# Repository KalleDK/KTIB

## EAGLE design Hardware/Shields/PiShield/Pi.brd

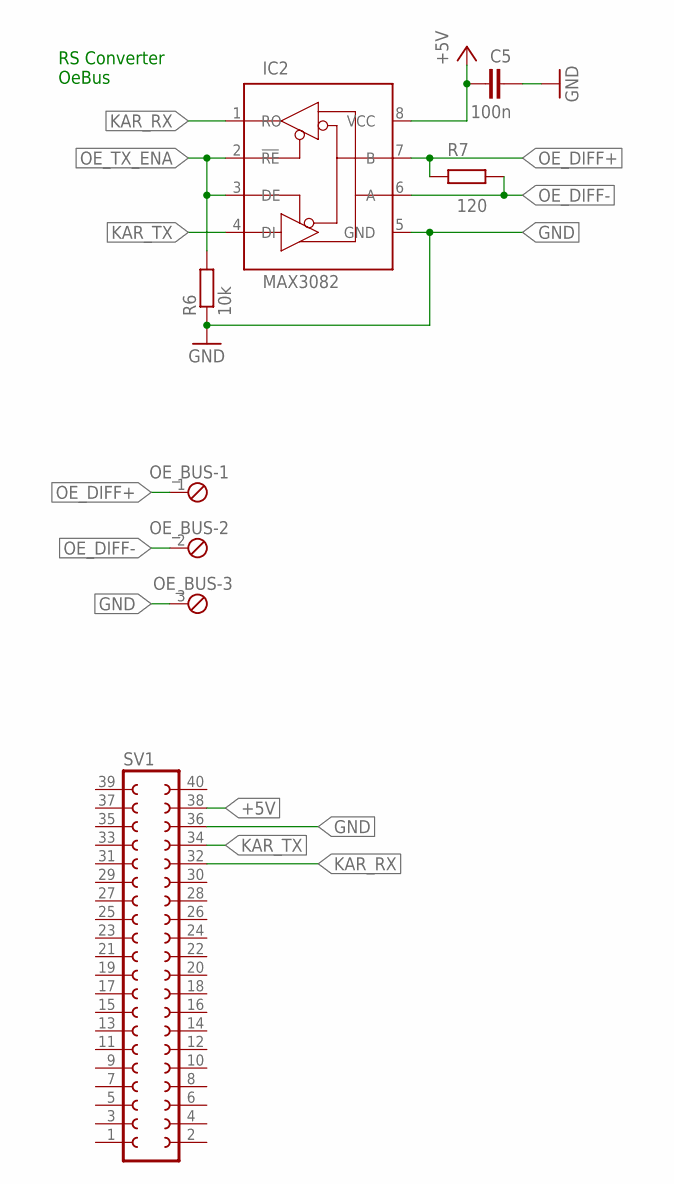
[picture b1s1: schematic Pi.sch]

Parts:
C5: 100n; C5B3
IC2: MAX3082; DIL08
OE_BUS: MPT3; 3POL254
R6: 10k; 0207/12
R7: 120; 0207/12
SV1: FE20-2

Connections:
+5V: SV1.38
GND: C5.2, IC2.5 (GND), OE_BUS.3, R6.1, SV1.36
KAR_RX: IC2.1 (RO), SV1.32
KAR_TX: IC2.4 (DI), SV1.34
OE_DIFF+: IC2.7 (B), OE_BUS.1, R7.2
OE_DIFF-: IC2.6 (A), OE_BUS.2, R7.1
OE_TX_ENA: IC2.2 (!RE!), IC2.3 (DE), R6.2
VCC: C5.1, IC2.8 (VCC)

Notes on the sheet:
RS Converter OeBus

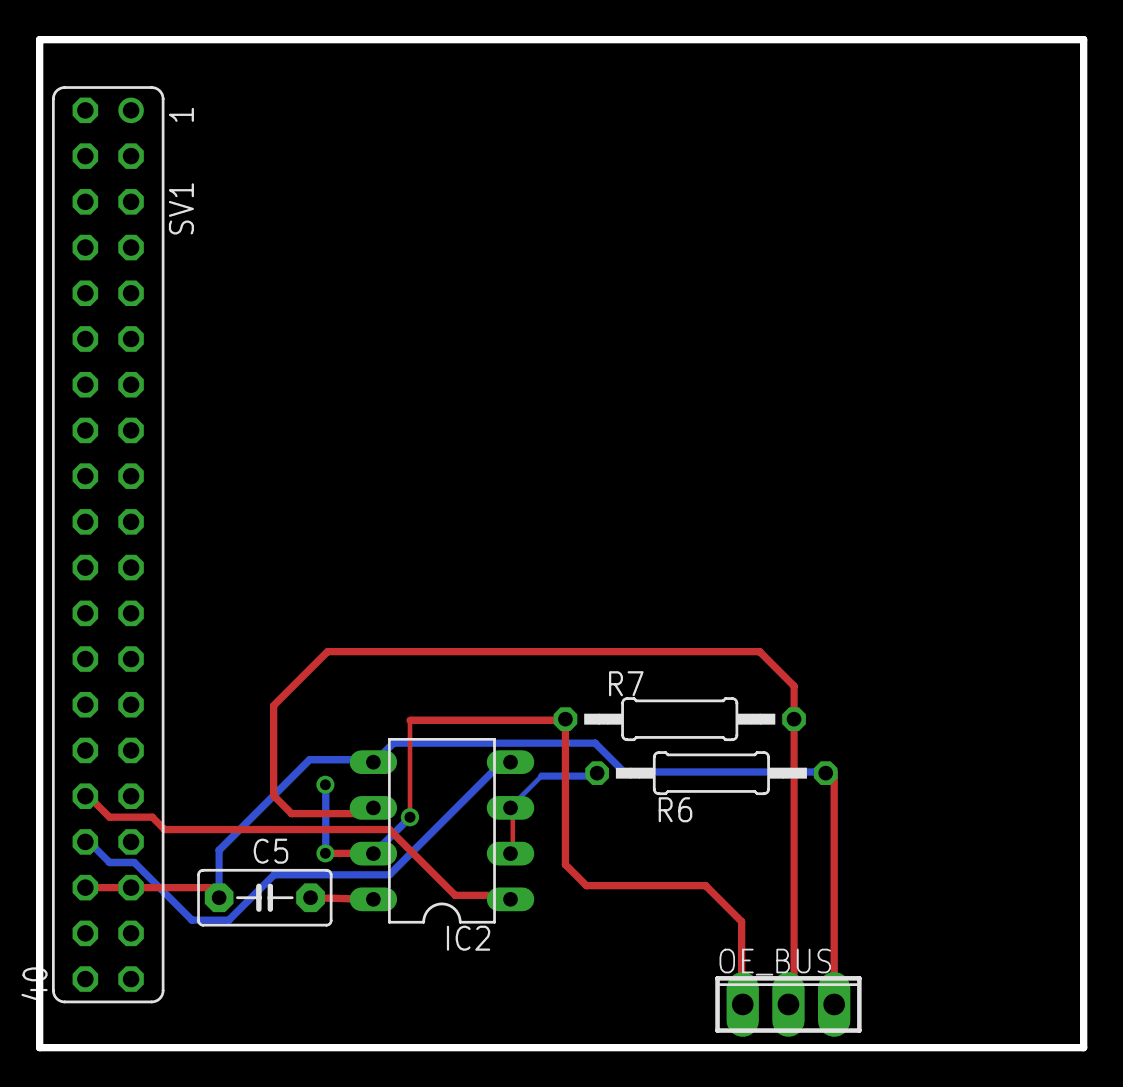
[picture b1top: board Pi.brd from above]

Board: 2 copper layers, 58.0 x 56.0 mm, 6 parts (0 on the bottom side), 7 nets.

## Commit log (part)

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2015-03-16 Systemarkitektur
2015-03-16 Fixes #40
2015-03-16 Ændringer til use case 2,3,4 og oprettelse af 5 og 6
    Oprettede use case 7 kalibrer pH-probe
    Ændringer fra i formiddags
    Flere rettelser
2015-03-17 Flyttet diagrammer
    Diagrammer er flyttet fra dropbox og ind i git, der er også oprettet
    mapper til system arkitektur
2015-03-17 Tilføjet Datablade
    Datablade til RS232 til RS485 konverteren
2015-03-17 opdaterede diagrammer KE
2015-03-17 KarControl added KE
2015-03-17 oprydning KE
2015-03-17 edits diagrammer KE
2015-03-17 Systemdiagram opdateret KE
2015-03-17 AVS domain model opdateret KE
2015-03-17 PSoC er weird
2015-03-17 flowchart added
2015-03-17 Rettelser til diagrammer
    Tilføjet og rettet i diverse diagrammer
2015-03-18 Opsætning af dokument til sys ark
    Har sat dokumentet op til system ark
2015-03-18 KarControl edits KE
2015-03-18 edit AVS domain model KE
2015-03-18 edits KarControldiagrammer KE
2015-03-18 Convert To PNG
2015-03-18 Ændret navne på visio filer og sat tex op
2015-03-18 Rettet visiofiler til kun at have en side
2015-03-18 Opdaterede system ark tex
2015-03-18 Der er lavet indtil videre
2015-03-18 Sensor Ø Allokerings diagram
    Sensor Ø BDD diagram
    Sensor Ø BDD opdateret
    BDD Opdateret og IBD
    IBD Implementeret
    Rettelse af IBD og BDD
2015-03-18 Ventilstyring rettet til
2015-03-18 Rettet navne og inout
2015-03-18 Sensor Library Added
2015-03-18 Ændres BDD og IBD pH-probe og jordfugt
2015-03-18 phProbe opdateret
2015-03-18 Jordfugt bdd og ibd opdateret
2015-03-18 IBD + BDD rettelser
2015-03-18 Domain model rettet
2015-03-18 nye png'er
2015-03-18 edits KE
2015-03-18 Signal beskrivelser
    For karcontrol
2015-03-18 Indsat beskriveleser
2015-03-18 Rettelser og beskrivelser
    I sys ark
2015-03-18 Vandpumpe indsat i tex
2015-03-18 Update af PNG
2015-03-18 Update af PNG'er
2015-03-18 Signal beskrivelser
2015-03-18 Små rettelser
2015-03-19 Massive oprydning og flere funktioner
2015-03-19 AllokeringsDiagram -> Allokeringsdiagram
2015-03-19 Noget vi ikke snakker om :panda_face:
2015-03-20 Indsat massere af fixmes
2015-03-20 fixes#116
2015-03-20 CentralControl_signalbeskrivelse_rettet #118
2015-03-20 KarControl edit KE #118
2015-03-20 Sesnor Ø + KarControl edits KE #118
2015-03-20 Fieldsensor edits KE #118
2015-03-20 Sensor_Jordfugt edits KE #118
2015-03-23 Opdateret UC og aktør diagrammer
2015-03-23 Fjernet plante som aktør og rette UC1
    Har rettet UC1 så denne ligner de andre UC
2015-03-23 Fjernet fixmes
2015-03-23 fixme update KE
2015-03-23 fixe update KE
2015-03-23 Sensor_pH diagrammer update KE
2015-03-23 signalbeskrivelse update KE
2015-03-23 Diagrammer edits KE
2015-03-24 gitignore upadte KE
2015-03-24 Pumpe+ventil forsyning edit KE
2015-03-24 Moved balde to blade
2015-03-25 Systems overordnede SD
2015-03-25 Sensor Ø Statemachine og Polling af Fieldsensors
2015-03-25 Tilføjet note
2015-03-26 Opdateret diagram
2015-03-27 PSU tilføjet til KarControl BDD/IBD
    PSU og RSConverter systemarkitektur aflyst
2015-03-31 Doseringspumpe + tex added KE
2015-04-03 Gitignore og header lavet for psoc
2015-04-03 Fieldsensor skabelon
2015-04-03 RS485 Protocol test
2015-04-03 Topdesign
2015-04-03 Rettet headerfil
2015-04-03 SensorOE I2C Done
2015-04-03 Intro Uart
2015-04-04 Removed all unused
2015-04-04 Updated SensorOe
    Changed from MsgQue to Bus
    And sender to transmitter
2015-04-04 Rettet hardcoded adresser
2015-04-04 tex updated med alaign KE
2015-04-04 HW- Ventilstyring added KE
    Ventilstyring i tex added KE
    tex updateret med align KE
2015-04-04 Beskrivelse af design til jordfugt og pH
    Design af jord fugtmåleren er beskrevet
2015-04-08 Interface beskrivelse i kravS.
    ordet planter fjernet fra Use case beskrivelsen.
2015-04-09 AVS Psoc Library
    SensorBus start
    RS485 uint16 to uint8
    Many changes to the lib
    Moved clear due to timing issue
    Fieldsensor complete
    Update topdesign
2015-04-09 Jordfugt tilføjet
    Software til PH probe tilføjet
    Debug added
    Move PHProbe
2015-04-09 Jordfugt opdateret
2015-04-10 Flow_Sensor_teknologiundersøgelse tex. added KE
2015-04-12 Fixed latex build
2015-04-12 Fix latex build 2
2015-04-13 First version
2015-04-14 Changed to inherit from MessageThread
2015-04-14 Changed to 100% event driven
2015-04-14 Removed unused member
2015-04-15 Mulig gjort compiling
2015-04-16 Removed unused Makefile (for DevKit)
2015-04-17 RS485 og Karbus
2015-04-17 Changed names to follow convention
2015-04-17 Kan kompile KarBus
2015-04-17 Doseringspumpe update KE
2015-04-17 --Se bort fra dette
2015-04-17 Revert "-"
    This reverts commit 4853a5b853914ae404497614156010ebdd29153f.
2015-04-17 rm hardcoded data
2015-04-17 askjdh
2015-04-18 Tilføjet Ventil
    Oprettet Doseringspumpe samt test til denne
    Kar opdateret
    Opdateret debug help
    Kar bygges
    RS485
    Karbus imple alpha
2015-04-18 Mere debug på kar
2015-04-18 Added RS485 test program
2015-04-18 iauhsd
2015-04-18 Awesome webinterface
2015-04-18 Removed old source
2015-04-18 Added new source
2015-04-18 KarBus nye enums
2015-04-18 Casper er gammel
2015-04-19 KarBusMessages included
2015-04-19 Ventilstryrings schematics update KE
2015-04-19 Doseringspumpe schematics update KE
2015-04-19 Sekvensdiagram til UC7
2015-04-19 Added event classes
2015-04-19 Added calls to parent constructor
2015-04-19 Removed something that wasn't supposed to be there
2015-04-19 rettet volumen stavefejlen
2015-04-19 Removed temp files
2015-04-19 Event based Karbus
2015-04-20 RS485 Flaf
2015-04-20 Init tools
2015-04-21 Flow_Sensor_Doku added KE
2015-04-21 Teknologiundersøgelser.tex update KE
2015-04-21 FlowSensor Datablad added KE
2015-04-22 FlowSensor Update KE
2015-04-22 sd_UC3 + sd_UC7 update KE
2015-04-23 fejl
2015-04-23 Revert "fejl"
    This reverts commit 0b0ff301740a99222c7b5b5150730c6ae1d1a0f7.
2015-04-25 Beskrivelse af design til jordfugt og pH
    Design af jord fugtm�leren er beskrevet
    pH dokumentation oprettet
    Billede tilf�jet
    Opdateret tekst
    Updated .gitignore
    Clening git ignore
2015-04-25 Fixing latex
2015-04-25 Klasse diagrammer
    Klasse diagrammer er sat ind i systemarkitektur.
    Jeg har også rettet lable i preamplen, så vi ikke får alle de ??
    problemer.
2015-04-26 Removed unneeded zip
2015-04-26 SensorOe Implemented
2015-04-26 Kar implementeret
2015-04-27 kar.class function
2015-04-28 Added session support for socket clients
2015-05-01 kode til ph probe indsat i latex
2015-05-01 Software til jordfugt proben opdateret og testet
2015-05-01 Added sensor data logging
2015-05-01 Made cross compiling makefile
    Protocol osv.
    Makefile og lidt protocol
    Karbus med working protocol
2015-05-01 Karbus ist better
2015-05-03 Added common defines file
2015-05-03 Something
2015-05-11 KarBús spiller
2015-05-11 Permisson changed
2015-05-13 Fixet kompiler goejl
2015-05-13 id -> Addr
2015-05-13 Empty
2015-05-15 Removed unused getData methods
2015-05-15 Changed use of OE id to address
2015-05-15 Changed id to address
2015-05-15 tilføjede software til ph-probe
2015-05-15 Addedd support for reading sensor data plus autoupdating buttons
2015-05-15 Added add sensor event from GUI
2015-05-15 Added pHProbe component
    Removed uneeded files
2015-05-17 ændrede kode til pH-proben
2015-05-17 Added flowsensor
2015-05-17 Flow sensor done
2015-05-18 Retteleser i web
2015-05-18 rettet Use case + acceptest
    der er også tilføjet en noget til glossary.
2015-05-19 Fixed bug where IVALVECLOSE doesnt work
2015-05-19 Fixed socket
2015-05-19 opdaterede latex og software til jordfugt
2015-05-20 gui + database dokumentation
2015-05-20 rettelser til accepttest
2015-05-20 Rettet overordnede sekvensdiagram og klasse diagram
2015-05-21 type 3 er rettet til 9
2015-05-21 Tilføjet dokumenter
2015-05-21 KarShield WIP KE
    Shields added KE
    Shield schematic added KE
    HW-arkitektur.tex Shields added KE
    Shields.tex KE
    brd deleted KE
    .sch update KE
2015-05-21 PSU multisim tilføjet
    Foreløbig idé.
    FET Datablad tilføjet
    DiodeBro datablade
    Strømforbrugsudregninger
    Mere dokumentation.
    Små rettelser i tekst
2015-05-21 Rettelsere inden accepttest
2015-05-21 Latex ph fix
2015-05-21 Latex Fix PNG
2015-05-21 Acceptest gennenført
2015-05-21 PSUdokumentation
    Analysedel 90% færdig.
2015-05-22 formatering af UC´s KE
2015-05-22 UC´s format update KE
2015-05-22 LH_grafiskbeskrivelse#99
    grafisk beskrivels af vandveje og systemmet overordnet
2015-05-22 Grænseflader til pH-probe og jordfugt
2015-05-22 Pumpe+shield update KE
2015-05-22 PSU + RSConverter
    95% færdig dokumentation
2015-05-22 MathCad udregning af Transformerparametre
2015-05-22 Sat template ind til flex pms dok
2015-05-22 PSU grænsebeskrivelse tilføjet
2015-05-24 Removed unused prototype from class MessageQueue
2015-05-24 Wrapped debugging-events from GUI til Bridge in a DEBUG section
2015-05-24 Test funktions tabel
    Lavet command til funktionsbeskrivelser
2015-05-24 Mere dokumentation til www
2015-05-24 Pakkediagrammer
2015-05-25 Removed unused prototype remove_client
2015-05-25 Moved Socket server HOST and PORT to defines.h
2015-05-25 Removed unused module CommModule.h
2015-05-25 Removed unused members from Kar class
2015-05-25 Opdateret rapport
2015-05-25 Rapport
2015-05-25 Ventil
2015-05-25 DebugUart
2015-05-25 SensorBus
2015-05-25 AVSLib beskrivelse
2015-05-25 StubProjects
2015-05-25 Billeder tilføjet til pH og jordfugt
2015-05-25 KarKommunikation beskrevet
2015-05-25 Sharelatex fix
2015-05-25 ProjektbeskrivelseHW
    HW beskrivelser
2015-05-25 Fieldsensor
2015-05-25 SensorOe
2015-05-25 Removed unused code from KarContainer (code is inherited from DBContainer)
2015-05-25 Tilføjet flow og ph
2015-05-25 Beskrevet Oe funktioner
2015-05-25 Indsat hele karbus mangler detaljerede beskrivelser
2015-05-25 Oebus beskrevet
2015-05-26 Beskrivelser
2015-05-26 Software setup til report
2015-05-26 Dokumentation
2015-05-26 StøjAfsnit
2015-05-26 GO test program
2015-05-26 Pi Shield added KE
2015-05-26 Shield.te edit KE
2015-05-26 Resume og udviklingsværktøjer
2015-05-26 Metode og SogA
2015-05-26 Latex Fix
2015-05-26 Debug rettet
2015-05-26 Tilføjelser til fremtidigt arbejde
    ikke færdig
2015-05-26 Forkerte værdier fjernet
2015-05-26 Metoden
2015-05-26 Værktøjer beskrevet
2015-05-26 Rettelse
2015-05-26 Literatur tilføjet
2015-05-26 Opdateret hw beskrivelse
2015-05-26 Erfaring
2015-05-26 Psoc
2015-05-26 Changed some diagrams to newer versions
2015-05-26 Added some italic to text
2015-05-26 Indledning plus rettelser i flex
    Conflicts:
    Latex/Litteratur/litteratur.bib
2015-05-26 Systembeskrivelse added KSN/KE
2015-05-26 Flex + RS485
2015-05-26 Commented on use cases (FlexPMS)
2015-05-26 Uppercase
2015-05-26 Systemarkitektur_rapport
2015-05-26 Konklution
2015-05-26 GUI + Database
2015-05-26 Edit KE
2015-05-26 Projektafgrænsning
2015-05-26 Bigger pictures
2015-05-26 Added GUI Protokol description with reference in FlexPMS documentation
2015-05-26 Made new afgrænsning
2015-05-26 Cleanup
2015-05-26 Removed unused files
2015-05-27 Krav edit KE
2015-05-27 ResultatogDisku edit KE
2015-05-27 Skrevet opnåede erfaringer
2015-05-27 Revert "Revert "Skrevet opnåede erfaringer""
    This reverts commit 2aa146f189b43cdb0d7c75a055d078ebc2173a29.
2015-05-27 AVS.png ændret
2015-05-27 Resultater og diskution
2015-05-27 Added some references
2015-05-27 FremtidigtArbejde KE
2015-05-27 Misc small changes to FlexPMS doc
2015-05-27 Tried to conclusion
2015-05-27 last AVS.png
2015-05-27 Fixed gramma etc in conclusion
2015-05-27 Fixed spelling error on StateDiagram
2015-05-27 Tegninger tilføjet
2015-05-27 fxnote
2015-05-27 Sti til billeder ændret
2015-05-27 Tilføjet glossary
2015-05-27 diverse HW edits Dokumentation KE
2015-05-27 blaa hvis gls
2015-05-27 Fix reference
2015-05-27 TransformertestDone
2015-05-27 review pH + FremtidigArejde KE
2015-05-27 preamble
    two side + fixed problemer
    fodnoter i bunden
    mere afstand før sections
2015-05-27 Fixed some references
2015-05-27 Ingen fxnote
2015-05-27 Tilføjet arbejdsfordeling
2015-05-27 Bilag added KE
2015-05-27 Shields KE
